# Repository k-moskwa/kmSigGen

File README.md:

# kmSigGen
DDS Generator based on AD9833 and ATMega8A with WiFi support via ESP8266-01

Main features:
* generates square (5Vp-p), sine and triangle(0.6Vp-p) waves in the ~0.1Hz to 12.5MHz frequency range (with ~0.1Hz step regulation)
* user interface based on LCD 16x2 and single rotary encoder with button
* possibility to store and recall 4 presets
* possibility to control device via TWI/I2C interface
* optional ESP8266-01 module for controlling device via WWW (e.g. from mobile phone)
* localization (available English and Polish language)
* screen saver (when available in LCD)
* easy configuration process with single conifg.h file (with possibility to disable some modules)
* project files available for AtmelStudio7 and Eclipse 

Components:
* ATmega8A MCU @ 8MHz
* AD9833/9837 assembled module @ 25MHz
* LCD 16x2 screen
* rotary encoder with button
* resistors, capacitors, connectors as defined on schematics view
Optional components:
* ESP8266-01 module
* 2 x LED (power and debug)

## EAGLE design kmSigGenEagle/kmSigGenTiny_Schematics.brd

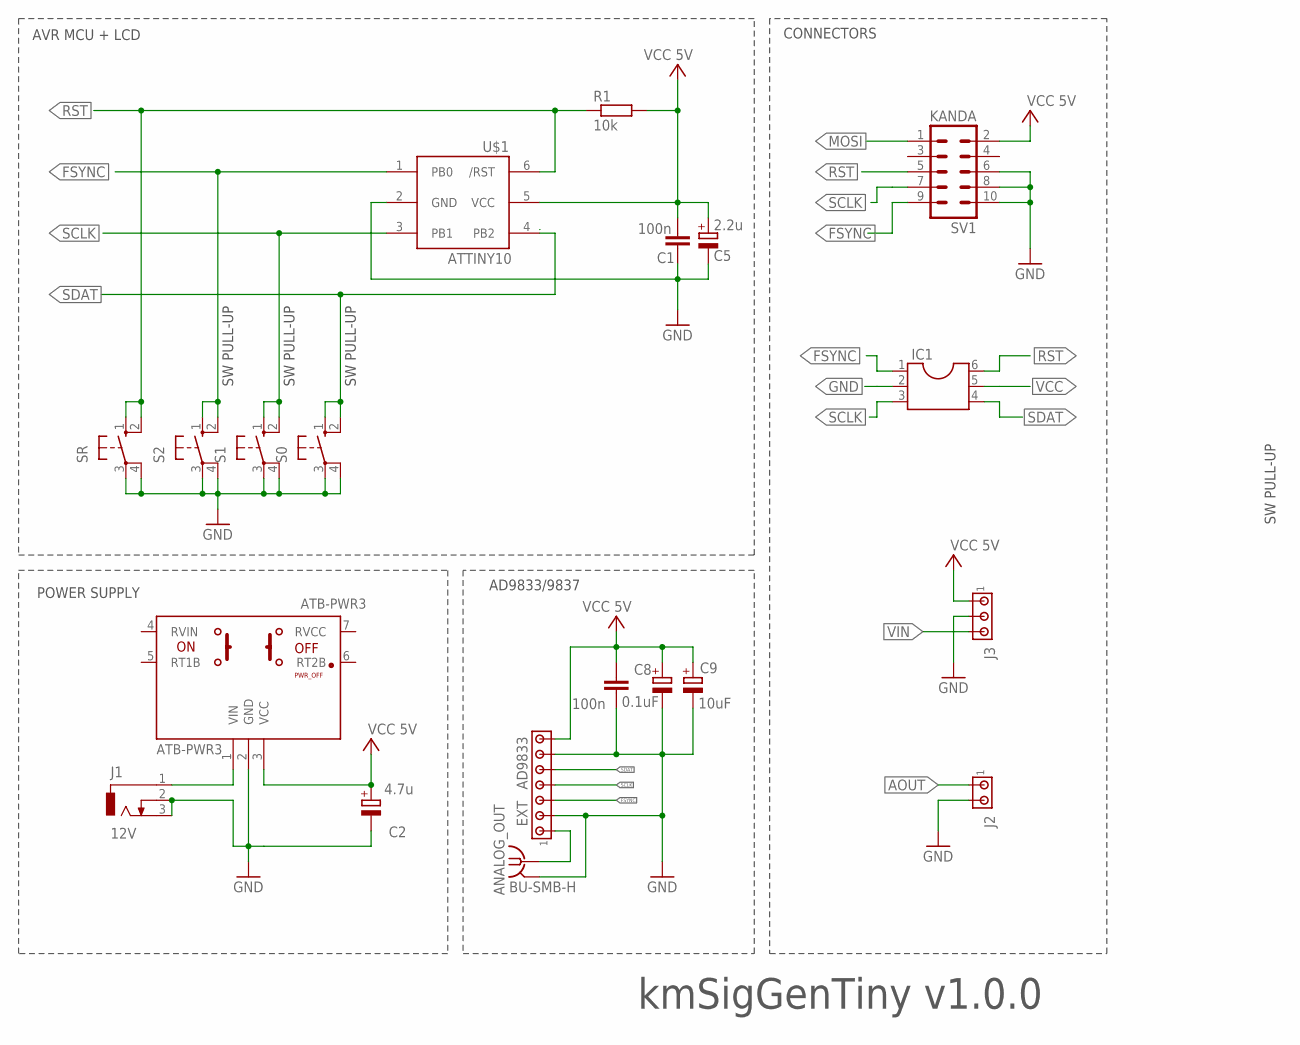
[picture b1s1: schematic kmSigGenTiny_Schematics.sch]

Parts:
ANALOG_OUT: BU-SMB-H
ATB-PWR3: ATB-PWR3
C1, C3: 100n; C2.5-4
C2: 4.7u; B45181B
C5: 2.2u; B45181B
C8: 0.1uF; B45181B
C9: 10uF; B45181B
EXT: AD9833; 10X07MTA
IC1: DIL6; DIL06
J1: 12V; DCJ0303
J2: MTA02-100; 10X02MTA
J3: MTA03-100; 10X03MTA
R1: 10k; 0207/10
S0, S1, S2: 10-XX; B3F-10XX
SR: 10-XX; B3F-10XX
SV1: KANDA; ML10
U$1: ATTINY10; SOT23-6

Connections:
AOUT: ANALOG_OUT.1, EXT.1, J2.1
FSYNC: EXT.3, IC1.1, S2.1 (S), S2.2 (S1), SV1.9, U$1.1 (PB0)
GND: ANALOG_OUT.2, ANALOG_OUT.3 (2), ANALOG_OUT.4 (2), ANALOG_OUT.5 (2), ATB-PWR3.2 (GND), C1.1, C2.-, C3.1, C5.-, C8.-, C9.-, EXT.2, EXT.6, IC1.2, J1.2, J1.3, J2.2, J3.2, S0.3, S0.4 (P1), S1.3, S1.4 (P1), S2.3, S2.4 (P1), SR.3, SR.4 (P1), SV1.6, SV1.8, SV1.10, U$1.2 (GND)
MOSI: SV1.1
RST: IC1.6, R1.1, SR.1 (S), SR.2 (S1), SV1.5, U$1.6 (/RST)
SCLK: EXT.4, IC1.3, S1.1 (S), S1.2 (S1), SV1.7, U$1.3 (PB1)
SDAT: EXT.5, IC1.4, S0.1 (S), S0.2 (S1), U$1.4 (PB2)
VCC: ATB-PWR3.3 (VCC), C1.2, C2.+, C3.2, C5.+, C8.+, C9.+, EXT.7, IC1.5, J3.1, R1.2, SV1.2, U$1.5 (VCC)
VIN: ATB-PWR3.1 (VIN), J1.1, J3.3

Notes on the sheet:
AD9833/9837
POWER SUPPLY
AVR MCU + LCD
CONNECTORS
kmSigGenTiny v1.0.0
SW PULL-UP

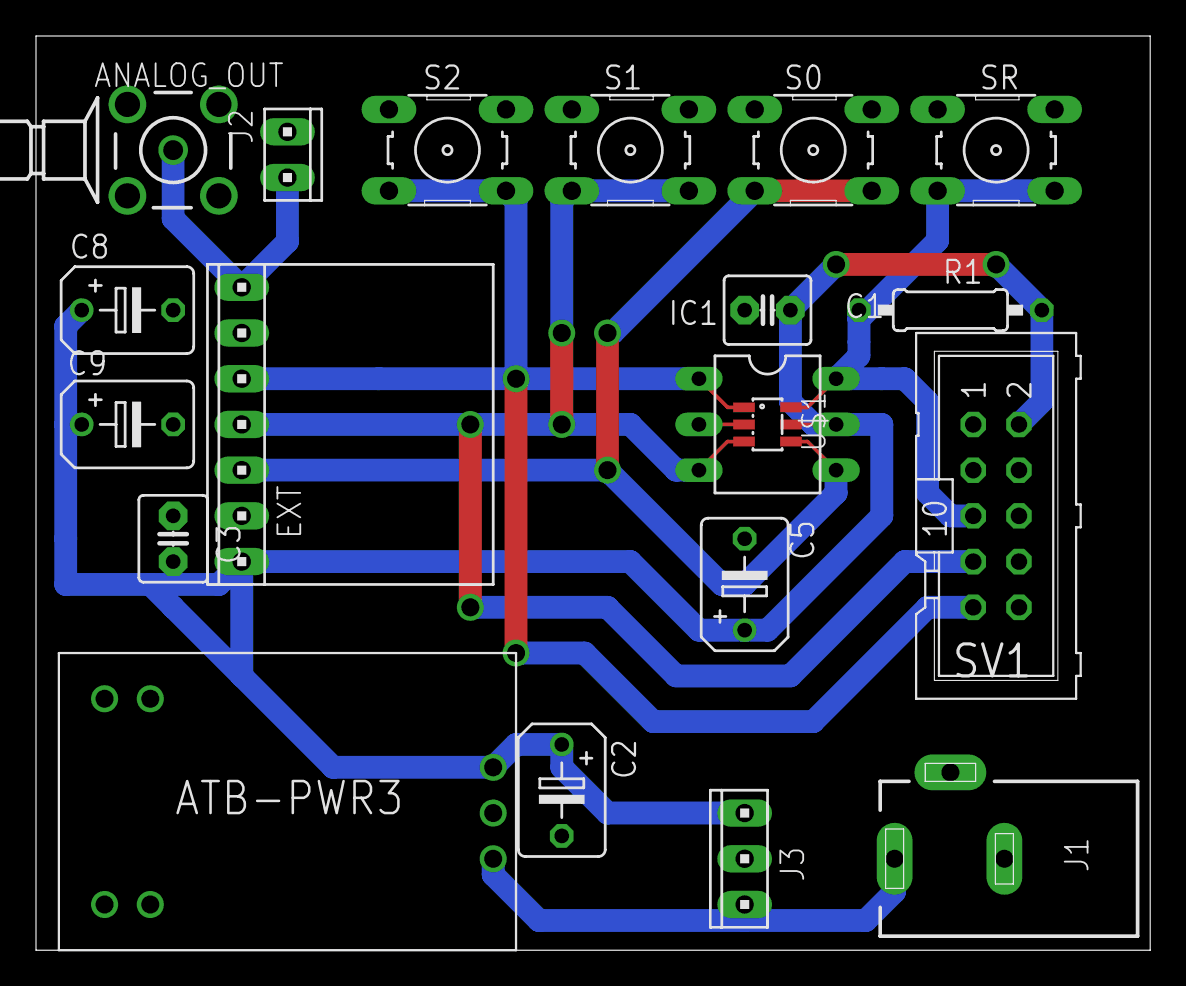
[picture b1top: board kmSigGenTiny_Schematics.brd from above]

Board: 2 copper layers, 61.9 x 50.8 mm, 20 parts (0 on the bottom side), 8 nets.

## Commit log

2019-07-21 Fixed issue with clearing wavetype after updating frequency from WiFi module; cleanup of Eagle Schematics, version changed to 1.0.1
2019-07-21 Updated schematics of encoder hardware
2019-07-21 Updatech schematics of encoder hardware
2019-07-23 Eclipse Project Added
2019-07-23 Eclipse build optimalization
2019-07-23 Default config changed to english version
2019-07-23 Solved issue with ESP8266 startup information; changed default colale to english version
2019-07-23 Version changed to 1.0.2
2019-07-27 Code cleanup after review (thx. Zealota & mirekk36 from https://forum.atnel.pl)
2019-07-27 Added power supply and update of schematics after review (thx. Zealota & mirekk36 from http://forum.atnel.pl)
2019-08-02 Added signal generator based on ATtiny10
2019-08-02 Support for Doxygen added
2019-08-02 Added Doxygen documentation
2019-08-02 Main docs file for githubpages redirecting to doxygen files
2019-08-02 Set theme jekyll-theme-time-machine
2019-08-02 Solving issue with doxygen file names starting with underscore (_)
2019-08-07 Solved potential source of problems when backlight pin is changed to different value (thx. anat from forum.atnel.com for helping to find it) + minor fixes
2019-08-17 KMSG-001 Added Support for ATB-ANDROMEDA development board
